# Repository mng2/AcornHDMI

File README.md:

# AcornHDMI
This is a design for a DVI/HDMI buffer, for use with the SQRL Acorn, an Artix-7 FPGA board originally intended for mining. It should also work with the RHS Research NiteFury/LiteFury, which are based on the same design as the Acorn.

Current status: revision A boards were assembled in late 2021. Working on bringup: [AcornHDMI-demo](https://github.com/mng2/AcornHDMI-demo)

## Why
The SQRL Acorn CLE-215+ consists of the largest Artix-7 FPGA, some DDR3 memory, and associated support circuitry. Since it was designed as an accelerator board in M.2 format, it does not have much in the way of user I/O, merely 4 LVDS pairs on a 2.5V bank, and 2 pairs on a 3.3V bank.

Four pairs banked together is not much, but it is just enough for a DVI or HDMI interface to an external monitor. The remaining issue is the physical layer: while Xilinx does support a TMDS I/O standard on this FPGA, it's only on 3.3V banks and the four pairs are on 2.5V. There are several ways to fix this, such as modding the board, but the more boring approach is to add a chip designed for the purpose. Plus if you're going to have to lay out a PCB anyway for the connectors, might as well make a whole project of it! (Says the guy with too many projects...)

For this board the PTN3381B fits the bill. Besides buffering into TMDS outputs, it handles level shifting for the Display Data Channel interface and hotplug detect, and generates 5V for the downstream device. Plus it does some other things that are probably unnecessary.

## Chips Used
- **PTN3381B** (NXP): 
NXP makes a number of video interface translation chips, including this one which seems to be intended to take DisplayPort (electrical-wise) and output TMDS. Each input is capacitively coupled and terminated into 50 ohms, so in theory an LVDS diff pair will "see" the 100 ohms it expects. The B version of the part supports up to 1.65 Gbit/s operation, and the D version supports 3 Gbit/s; however a -3 speed grade Artix-7 only goes up to 1250 Mbit/s, so the D is overkill. From a cursory examination, the only difference in the pinout is how the pre-emphasis is configured, so it should be possible to support both models. (Note that the D version is going EOL.)
- **PCA9534** (NXP, TI): 
This is an I2C expander with 8 bits of real FET drive output, as opposed to the weird weak drive that other models use. The I/O bits are used to configure the PTN3381 for the most part. One output is earmarked for the statutory minimum complement of one (1) blinkenlight. CEC is a stretch goal...

## Connectivity
The Acorn has the relevant I/O on a Hirose DF52 connector. This 0.8mm pitch system is a wonder of engineering but not too much fun to play with. Your faithful correspondent has tried and failed to make a 3M 7700-series based DF52 cable, and can only recommend the use of Hirose's pre-crimped wires. If only they were a little bit cheaper...

## PCB Design
This board was designed in KiCAD 5.1.something, with OSH Park's 4-layer board service in mind. The total area is a bit under 1.5 square inches, which translates to ~$15 for 3 copies. The differential pairs are constrained for the defined stackup, with ground on layer 2, though connections are pretty short and there was no attempt to length-match.

My board design philosophy is to not push the limits if there's no need to, so while the spec at OSH Park is 5/5, I chose to use widths starting at 6 mils. There is one DRC complaint, eminently ignorable, which is that the silk for C2 slightly overlays the pad for C3.

Note that this board uses HLV technology for the QFN pad. HLV (Hilariously Large Via) technology is probably incompatible with reflow processes -- this layout was designed for hand soldering, and utilizes the "hand soldering" variants of the surface mount components in the default library. If you intend to do reflow you will want to redesign with the appropriate footprints. (Or do the HLV by hand, or perhaps it is OK? With small vias the solder tends to get sucked in, pulling the part down to the board. It may be less of an issue for standard QFNs.)

## Assembly
* The secret to SMT assembly is magnification. Things are not so difficult when you can see them. I would not try to put this together without some kind of microscope or USB microscope.
* The other secret is experience. I think some experience with fine-pitch soldering is necessary. 
Speaking for myself, knowing how to recover from making a mess is essential, using flux and braid.
* A fine-pitch temperature-controller soldering iron is advised, or hot air. I think I used Hakko tip T18-C05, a fine beveled shape. This is more for the QFN and fine-pitched stuff, 0603 and up benefits from the heat transfer of something bigger.
* I would put U1 and the backside 0402s on first, they are harder to deal with when the board does not lie flat. 

## Errata
* LEDs too bright. I designed for 10mA but I would aim for 1mA or less.

## Links

## License
CERN OHL v2 Permissive

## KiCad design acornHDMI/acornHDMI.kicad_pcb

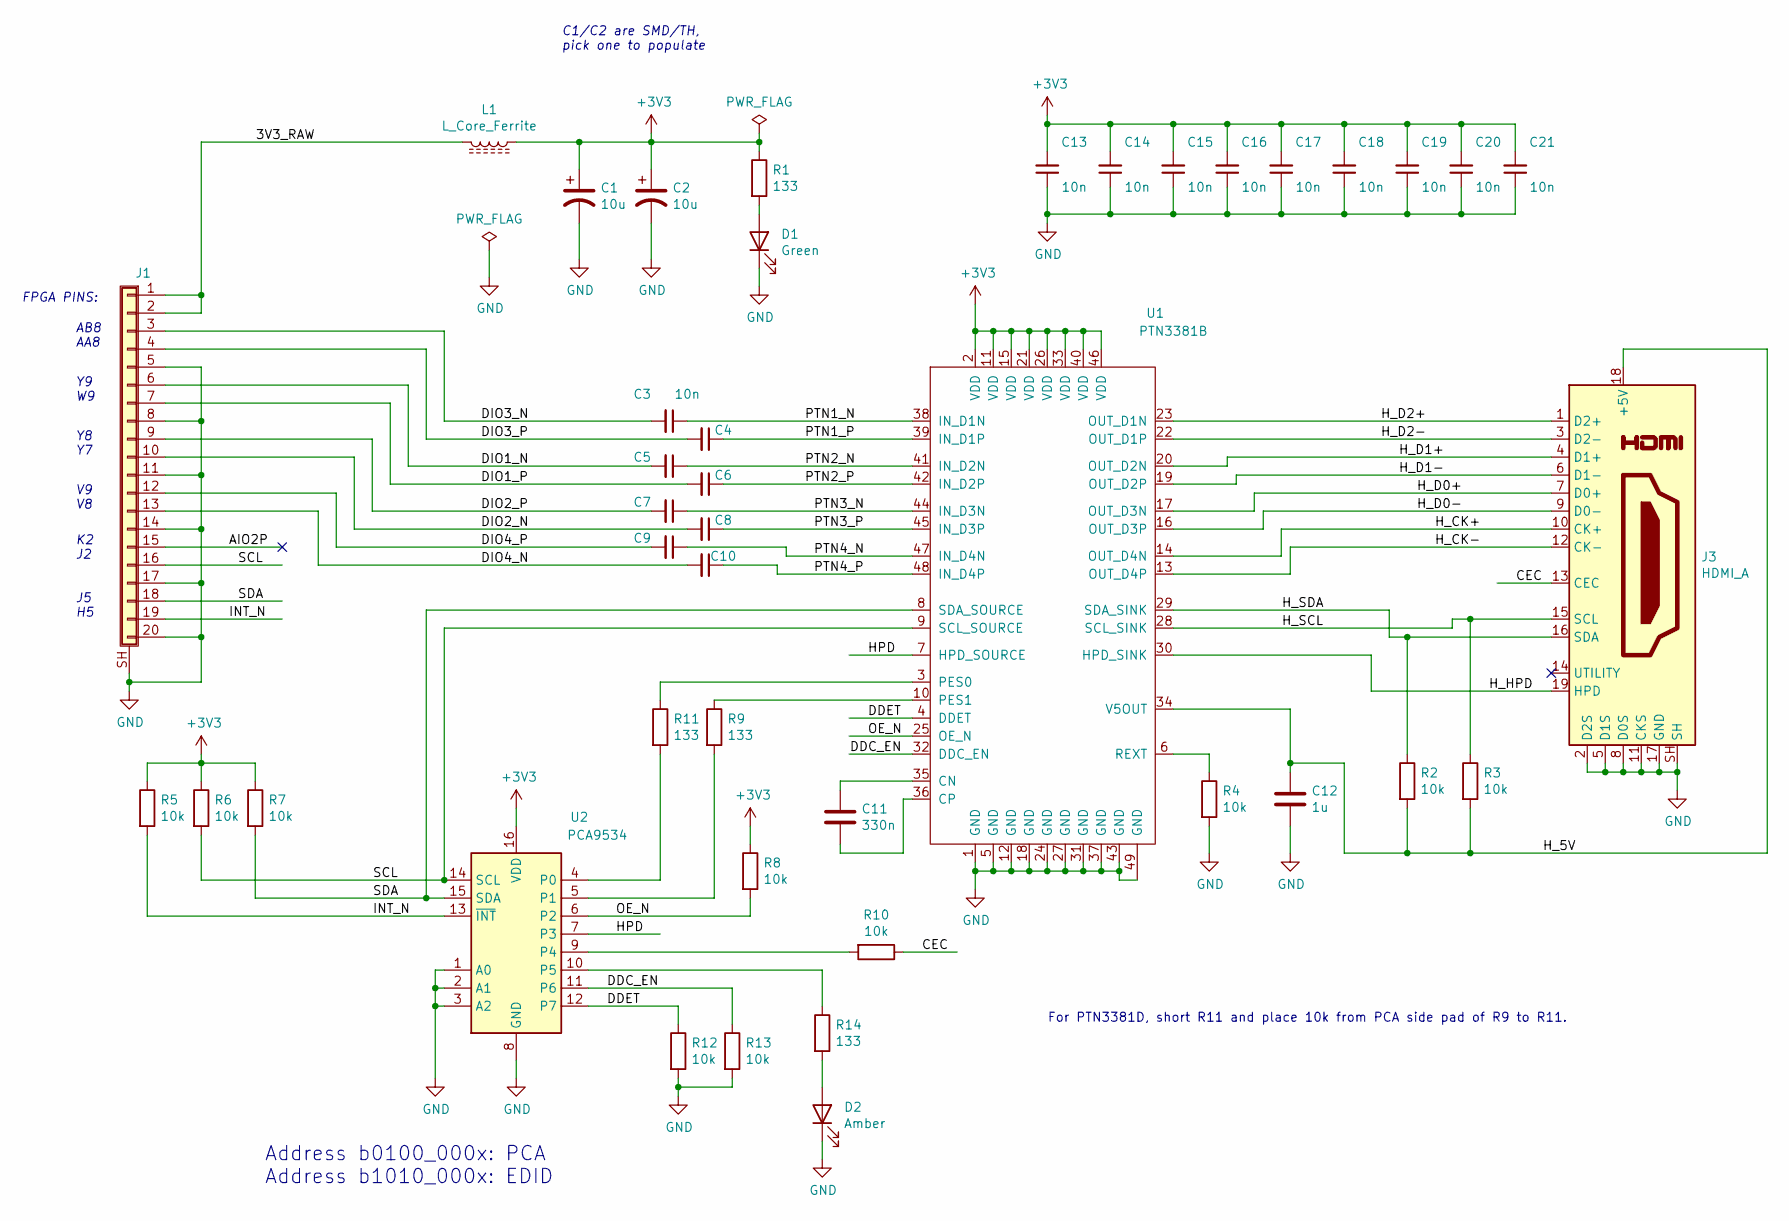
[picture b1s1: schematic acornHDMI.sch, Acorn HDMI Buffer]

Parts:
C1: 10u; C_1206_3216Metric_Pad1.33x1.80mm_HandSolder
C2: 10u; CP_Radial_D5.0mm_P2.50mm
C3, C4, C5, C6, C7, C8, C9, C10, C13, C14, C15, C16, C17, C18, C19, C20, C21: 10n; C_0402_1005Metric_Pad0.74x0.62mm_HandSolder
C11: 330n; C_0603_1608Metric_Pad1.08x0.95mm_HandSolder
C12: 1u; C_0603_1608Metric_Pad1.08x0.95mm_HandSolder
D1: Green; D_1206_3216Metric_Pad1.42x1.75mm_HandSolder
D2: Amber; D_1206_3216Metric_Pad1.42x1.75mm_HandSolder
J1: Conn_01x20_Shielded; DF52-20-S0.8H_handsoldering
J3: HDMI_A; 10029449-111
L1: L_Core_Ferrite; L_1206_3216Metric_Pad1.42x1.75mm_HandSolder
R1, R9, R11, R14: 133; R_0603_1608Metric_Pad0.98x0.95mm_HandSolder
R2, R3, R4, R5, R6, R7, R8, R10, R12, R13: 10k; R_0603_1608Metric_Pad0.98x0.95mm_HandSolder
U1: PTN3381B; QFN-48-1EP_7x7mm_P0.5mm_EP5.15x5.15mm
U2: PCA9534; TSSOP-16_4.4x5mm_P0.65mm

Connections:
+3V3: C1.1, C2.1, C13.2, C14.2, C15.2, C16.2, C17.2, C18.2, C19.2, C20.2, C21.2, L1.1, R1.1, R5.1, R6.1, R7.1, R8.1, U1.2 (VDD), U1.11 (VDD), U1.15 (VDD), U1.21 (VDD), U1.26 (VDD), U1.33 (VDD), U1.40 (VDD), U1.46 (VDD), U2.16 (VDD)
/3V3_RAW: J1.1, J1.2, L1.2
/AIO2P: J1.15
/CEC: J3.13 (CEC), R10.1
/DDC_EN: R13.1, U1.32 (DDC_EN), U2.11 (P6)
/DDET: R12.1, U1.4 (DDET), U2.12 (P7)
/DIO1_N: C5.2, J1.6
/DIO1_P: C6.2, J1.7
/DIO2_N: C8.2, J1.10
/DIO2_P: C7.2, J1.9
/DIO3_N: C3.2, J1.3
/DIO3_P: C4.2, J1.4
/DIO4_N: C10.2, J1.13
/DIO4_P: C9.2, J1.12
/HPD: U1.7 (HPD_SOURCE), U2.7 (P3)
/H_5V: C12.1, J3.18 (+5V), R2.2, R3.2, U1.34 (V5OUT)
/H_CK+: J3.10 (CK+), U1.14 (OUT_D4N)
/H_CK-: J3.12 (CK-), U1.13 (OUT_D4P)
/H_D0+: J3.7 (D0+), U1.17 (OUT_D3N)
/H_D0-: J3.9 (D0-), U1.16 (OUT_D3P)
/H_D1+: J3.4 (D1+), U1.20 (OUT_D2N)
/H_D1-: J3.6 (D1-), U1.19 (OUT_D2P)
/H_D2+: J3.1 (D2+), U1.23 (OUT_D1N)
/H_D2-: J3.3 (D2-), U1.22 (OUT_D1P)
/H_HPD: J3.19 (HPD), U1.30 (HPD_SINK)
/H_SCL: J3.15 (SCL), R3.1, U1.28 (SCL_SINK)
/H_SDA: J3.16 (SDA), R2.1, U1.29 (SDA_SINK)
/INT_N: J1.19, R5.2, U2.13 (~INT~)
/OE_N: R8.2, U1.25 (OE_N), U2.6 (P2)
/PTN1_N: C3.1, U1.38 (IN_D1N)
/PTN1_P: C4.1, U1.39 (IN_D1P)
/PTN2_N: C5.1, U1.41 (IN_D2N)
/PTN2_P: C6.1, U1.42 (IN_D2P)
/PTN3_N: C7.1, U1.44 (IN_D3N)
/PTN3_P: C8.1, U1.45 (IN_D3P)
/PTN4_N: C9.1, U1.47 (IN_D4N)
/PTN4_P: C10.1, U1.48 (IN_D4P)
/SCL: J1.16, R6.2, U1.9 (SCL_SOURCE), U2.14 (SCL)
/SDA: J1.18, R7.2, U1.8 (SDA_SOURCE), U2.15 (SDA)
GND: C1.2, C2.2, C12.2, C13.1, C14.1, C15.1, C16.1, C17.1, C18.1, C19.1, C20.1, C21.1, D1.1 (K), D2.1 (K), J1.5, J1.8, J1.11, J1.14, J1.17, J1.20, J1.SH (Shield), J3.2 (D2S), J3.5 (D1S), J3.8 (D0S), J3.11 (CKS), J3.17 (GND), J3.SH, R4.2, R12.2, R13.2, U1.1 (GND), U1.5 (GND), U1.12 (GND), U1.18 (GND), U1.24 (GND), U1.27 (GND), U1.31 (GND), U1.37 (GND), U1.43 (GND), U1.49 (GND), U2.1 (A0), U2.2 (A1), U2.3 (A2), U2.8 (GND)
unnamed: C11.1, U1.35 (CN)
unnamed: C11.2, U1.36 (CP)
unnamed: D1.2 (A), R1.2
unnamed: D2.2 (A), R14.2
unnamed: R4.1, U1.6 (REXT)
unnamed: R9.1, U1.10 (PES1)
unnamed: R9.2, U2.5 (P1)
unnamed: R10.2, U2.9 (P4)
unnamed: R11.1, U1.3 (PES0)
unnamed: R11.2, U2.4 (P0)
unnamed: R14.1, U2.10 (P5)

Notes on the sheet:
For PTN3381D, short R11 and place 10k from PCA side pad of R9 to R11.
K2 J2 J5 H5
AB8 AA8
Y9 W9
Y8 Y7
V9 V8
FPGA PINS:
C1/C2 are SMD/TH, pick one to populate
Address b0100_000x: PCA Address b1010_000x: EDID

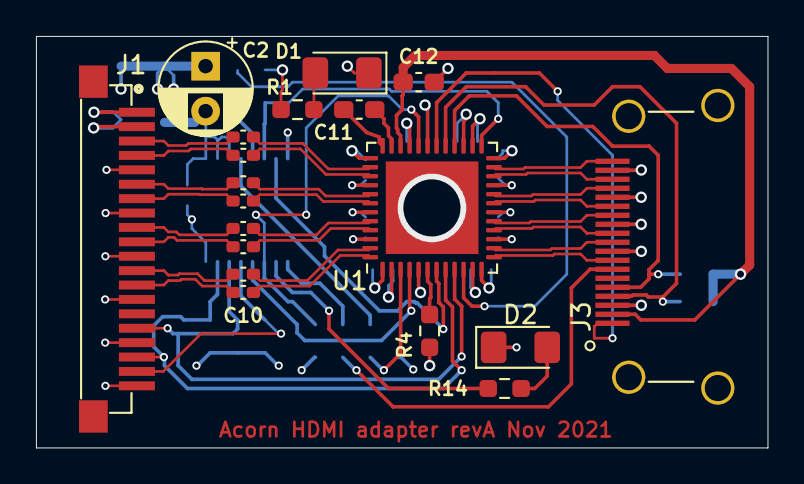
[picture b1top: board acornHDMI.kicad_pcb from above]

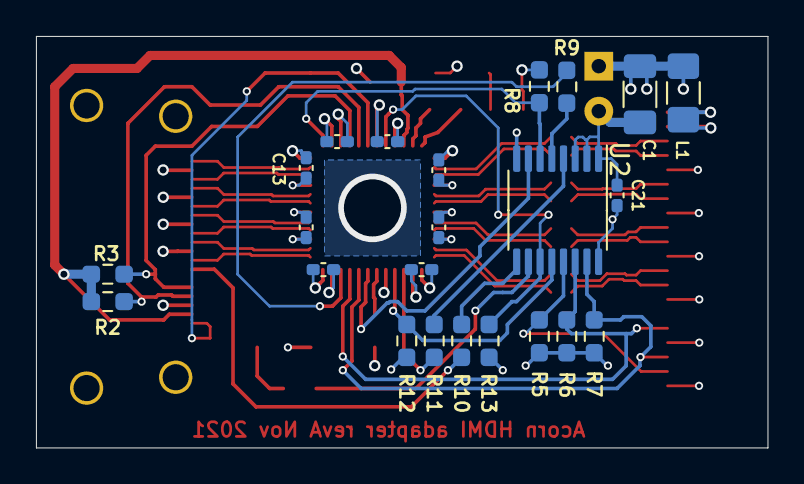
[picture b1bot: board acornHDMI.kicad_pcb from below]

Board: 4 copper layers, 40.6 x 22.9 mm, 42 parts (23 on the bottom side), 50 nets.

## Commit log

2021-07-03 initial checkin for git, work in progress
2021-07-03 start readme
2021-07-04 more readme
2021-07-08 change PTN3381D to B
2021-07-12 tighten up placement, start routing
2021-09-04 change to 3M 7700 cable
2021-09-04 routing in progress
2021-11-17 a bit of routing. need to reconsider connector
2021-11-18 make DF52 footprint
2021-11-26 add df52 to board. revise board edges, near finalization
2021-11-29 revA for initial production
2021-12-15 upload board pic
